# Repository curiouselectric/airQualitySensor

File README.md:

# airQualitySensor
This is a PCB and design for an air quality sensor unit using the [sensor.community](https://maps.sensor.community/) design

This is a PCB design (in KiCAD) and laser cut enclosure plate design to make an air quality sensor node for inclusion in the [sensor.community](https://maps.sensor.community/) global open environmental data platform .
I think the project is amazing and produced this design for a simplified, but robust DIY kit.

This is heavily based on these two open-source projects:

https://github.com/CivicLabsBelgium/influencair-pcb

https://github.com/Naesstrom/Airrohr-kit

The second link (by Erik Näsström) is a great design. I wanted to, very slightly, simplify this and produce a unit that does not need a 3d printer. I set about designing laser cut parts for this.

The PCB is very simple, but has been produced in the totally open-source PCB design package KiCAD.

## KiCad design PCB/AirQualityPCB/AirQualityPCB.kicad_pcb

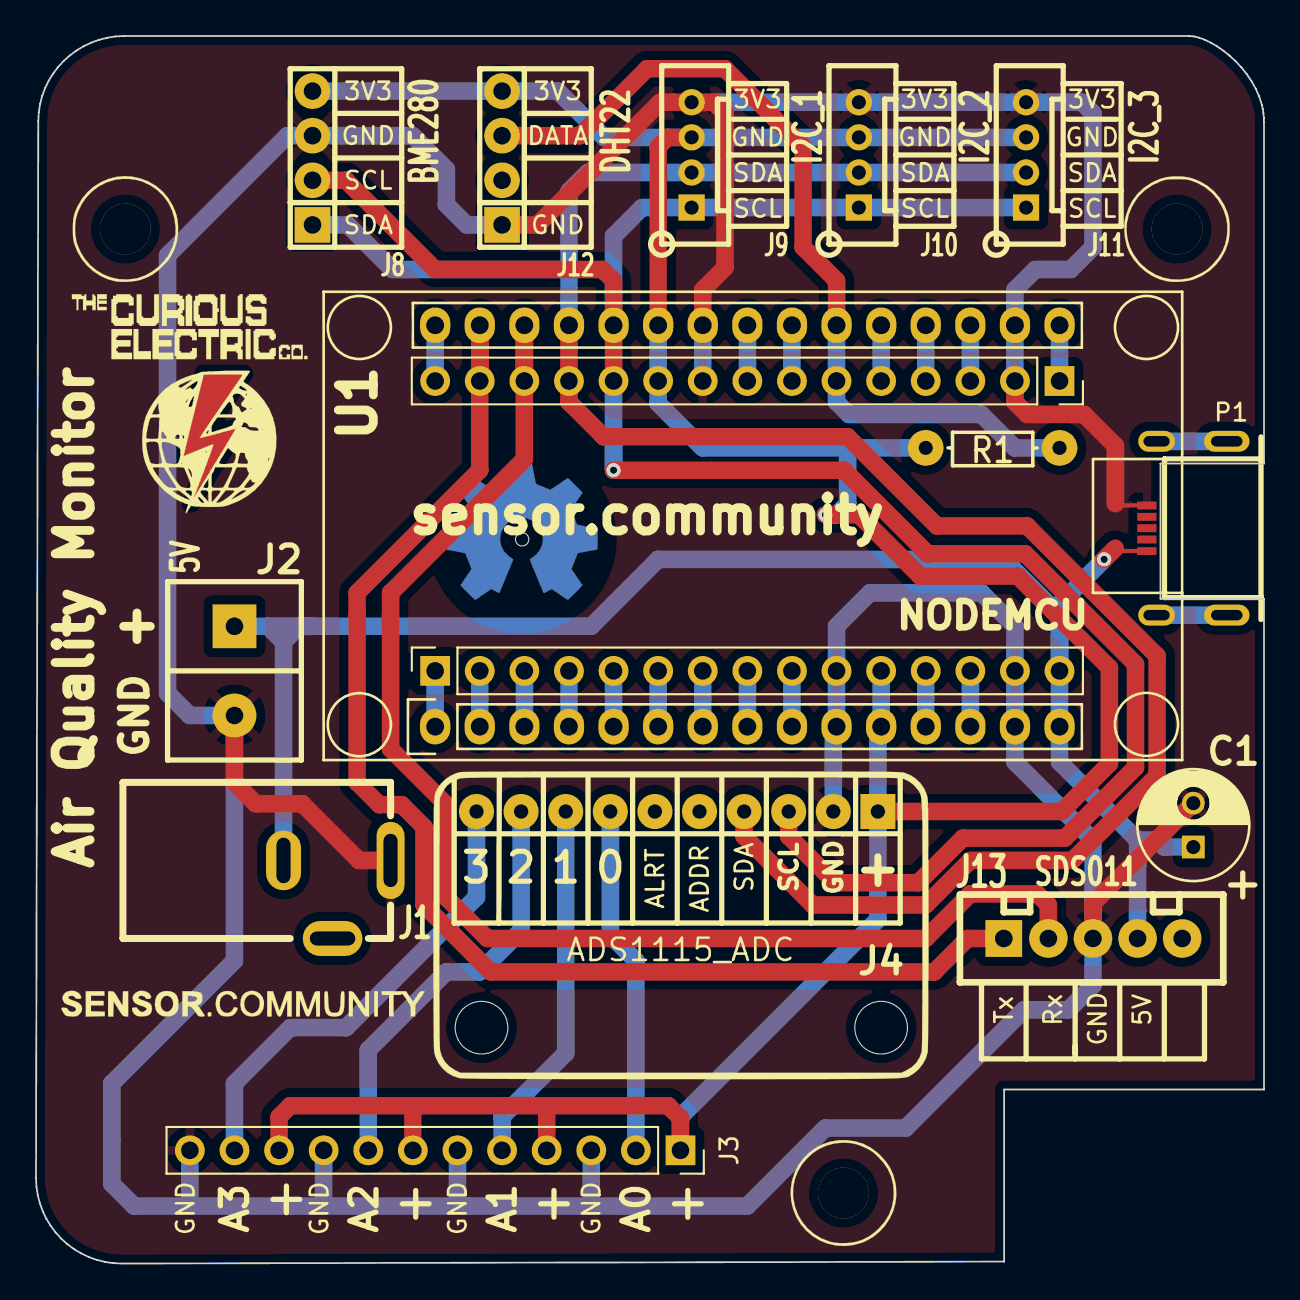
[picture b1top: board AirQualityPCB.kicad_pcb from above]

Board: 2 copper layers, 69.9 x 69.9 mm, 21 parts (1 on the bottom side), 30 nets.

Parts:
C1: 100uf; C_Radial_D6.3_L11.2_P2.5
J1: 5V; DC_Power_2_1
J2: 5V; SIL-2_screw_terminal
J3: ADC_IN; PinSocket_1x12_P2.54mm_Vertical_Labelled
J4: ADS1115_ADC; ADAFRUIT_ADS1115
J5: PCB; PCB_LuftDaten_70x70
J6: LOGO_OSW; OSHW_logo_small_back
J7: LOGO_TCEC; TCEC_Words_13mm
J8: BME280; SIL-4_large_pad_BME280
J9: I2C_1; SIL-4_Grove_Labelled
J10: I2C_2; SIL-4_Grove_Labelled
J11: I2C_3; SIL-4_Grove_Labelled
J12: DHT22; SIL-4_large_pad_DHT22
J13: SDS011; SIL-5_JST_5WAY_labelled
J14: ESP_BO1; PinSocket_1x15_P2.54mm_Vertical
J15: ESP_BO2; PinSocket_1x15_P2.54mm_Vertical
J16: LOGO_LUFTDATEN; sensorcommunity
J18: LOGO_TCEC; 2019_011_16_CuriousElectricCompany_Logo_Round_Logo_No_words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
P1: PWR; USB_Micro-B_MOLEX_47642-0001
R1: 4k7; TH_Resistor_1
U1: NODEMCU; NodeMCU_Amica_R2_FSILK

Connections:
+5V: C1.1, J1.1, J2.1, J13.4, J14.15, P1.1 (VCC), U1.15 (VIN)
/A0: J3.2, J4.7
/A1: J3.5, J4.8
/A2: J3.8, J4.9
/A3: J3.11, J4.10
/BME280_SCL: J4.3, J8.2, J9.1, J10.1, J11.1, J15.11, U1.26 (D4)
/BME280_SDA: J4.4, J8.1, J9.2, J10.2, J11.2, J15.12, U1.27 (D3)
/DHT22: J12.3, J15.6, R1.1, U1.21 (D7)
/PWR_3V3: J3.1, J3.4, J3.7, J3.10, J4.1, J8.4, J9.3, J10.3, J11.3, J12.4, J14.11, J15.10, R1.2, U1.11 (3V3), U1.25 (3V3)
/SDS011_RxD: J13.2, J15.13, U1.28 (D2)
/SDS011_TxD: J13.1, J15.14, U1.29 (D1)
GND: C1.2, J1.2, J2.2, J3.3, J3.6, J3.9, J3.12, J4.2, J8.3, J9.4, J10.4, J11.4, J12.1, J13.3, J14.10, J14.14, J15.2, J15.9, P1.5 (GND), U1.10 (GND), U1.14 (GND), U1.17 (GND), U1.24 (GND)
unnamed: J14.1, U1.1 (A0)
unnamed: J14.2, U1.2 (RSV)
unnamed: J14.3, U1.3 (RSV)
unnamed: J14.4, U1.4 (SD3)
unnamed: J14.5, U1.5 (SD2)
unnamed: J14.6, U1.6 (SD1)
unnamed: J14.7, U1.7 (CMD)
unnamed: J14.8, U1.8 (SD0)
unnamed: J14.9, U1.9 (SLK)
unnamed: J14.12, U1.12 (EN)
unnamed: J14.13, U1.13 (RST)
unnamed: J15.1, U1.16 (3V3)
unnamed: J15.3, U1.18 (D10)
unnamed: J15.4, U1.19 (D9)
unnamed: J15.5, U1.20 (D8)
unnamed: J15.7, U1.22 (D6)
unnamed: J15.8, U1.23 (D5)
unnamed: J15.15, U1.30 (D0)

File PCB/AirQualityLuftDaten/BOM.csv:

Reference, Value, Footprint, Datasheet
"U1","NODEMCU","REInnovationFootprint:NodeMCU_Amica_R2_FSILK",""
"J13","SDS011","REInnovationFootprint:SIL-5_JST_5WAY_labelled","~"
"J8","BME280","REInnovationFootprint:SIL-4_large_pad_BME280","~"
"J1","5V","REInnovationFootprint:DC_Power_2_1","~"
"J2","5V","REInnovationFootprint:SIL-2_screw_terminal","~"
"P1","PWR","REInnovationFootprint:USB_Micro-B_MOLEX_47642-0001",""
"J5","PCB","REInnovationFootprint:PCB_LuftDaten_70x70","~"
"J6","LOGO_OSW","REInnovationFootprint:OSHW_logo_small_back","~"
"J7","LOGO_TCEC","CuriousElectric3:TCEC_Words_13mm","~"
"J9","I2C_1","REInnovationFootprint:SIL-4_Grove_Labelled","~"
"J11","I2C_3","REInnovationFootprint:SIL-4_Grove_Labelled","~"
"J10","I2C_2","REInnovationFootprint:SIL-4_Grove_Labelled","~"
"R1","4k7","REInnovationFootprint:TH_Resistor_1","~"
"J12","DHT22","REInnovationFootprint:SIL-4_large_pad_DHT22","~"
"J4","ADS1115_ADC","REInnovationFootprint:ADAFRUIT_ADS1115","~"
"J14","ESP_BO1","Connector_PinSocket_2.54mm:PinSocket_1x15_P2.54mm_Vertical","~"
"J15","ESP_BO2","Connector_PinSocket_2.54mm:PinSocket_1x15_P2.54mm_Vertical","~"
"J16","LOGO_LUFTDATEN","CuriousElectric3:sensorcommunity","~"
"J17","LOGO_AirRohr","CuriousElectric3:logo_conversion","~"
"J18","LOGO_TCEC","CuriousElectric3:2019_011_16_CuriousElectricCompany_Logo_Round_Logo_No_words_KiCAD_10mm_PCBLogo","~"
"C1","100uf","REInnovationFootprint:C_Radial_D6.3_L11.2_P2.5","~"
"J3","ADC_IN","REInnovationFootprint:PinSocket_1x12_P2.54mm_Vertical_Labelled","~"

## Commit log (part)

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2020-06-14 Added PCB design and Hardware - initial commit
2020-08-10 Updated PCB and baseplate files
2020-08-10 Added Schematic and BOM
2020-08-20 Update on hardware design
2020-08-20 Updated instructions v1 final
    For public release
2021-06-24 updated instructions!
2023-03-28 updated instructions
2023-09-07 Updated PCB and instructions. Removed old names and links
2026-02-17 backup update
